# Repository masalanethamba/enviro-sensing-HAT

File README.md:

**GROUP 34**

**Description**

TheTemperature-Light sensor is a system that monitors and records
the temperature and light of a room or any place under consideration such that if the
temperature and the light are higher than required, the system displays it on the
computer. Similarly, if the temperature and the light are lower, the system displays it.
This System can also be connected to external Temperature/Light controllers.
Temperature/Light controller can be manual or automatic. The former requires full
human intervention to operate, while the latter requires little or not at all.
Furthermore, most temperature/light controller and related systems designed make
used of discrete components design such as timers, counters, decoder drivers and
thermistor temperature sensor and some use microcontrollers with external analogue
to digital converter (ADC) which is recommended for this system.
This system is powerful and very easy-to-program. It has 33-pins, and it has a
memory of 256-KB I2C of EEPROM data memory, self-programming.
Operating voltage range between 2V to 5V

**Getting Started with Temperature Sensor version5.1 and STM32CubeID**

**Introduction**
_________________________________________________________________________________

In this simple getting started how to document, we will be building a simple STM32CUBEID project (code) on a simple Temperature and Humidity Sensor uHAT. At its simplest/basic level the whole process of deploying  a code to the Temperature and Humidity Sensor PCB Version 5.1 consists of two “must do'' steps:

→ You would need to set your Temperature and Humidity Sensor with Group34OS, the  host OS which is responsible for  communication with the UCTCloud and also runs the core operations of the device

→  You need to also push your STM32CUBEID project image builder, which is responsible for pulling in all the important   
   dependencies and makes a container image for your fleet.
   
A completion of these steps implies that your Temperature and humidity Sensor Ver 5.1 will start to download the container image, begin your application, and start sending logs to your Group34 dashboard. This has got you at least a step towards success!

**What will you need?**
__________________________________________________________________________________
Hardware:

→ A Temperature and Humidity Sensor uHAT Ver5.1. You can also visit or GitHub repo and check out similar or related
                models.
                
→  18650-5V Li-ion battery for Power supply(optional) .

→ A simple micro USB mini cable for access to the CH340G transceiver and debugging

→ The micro USB can also be used for power supply.

→ Female connectors 

→ A syringe for water drops to acknowledge and appreciate the functionality of the sensors.

→ The STM32F051 UCT discovery board for the Cortex-M0 microcontroller interfacing.

→ A Group34 account/ link

→ Github account   

Software :
    →  STM32CUBEIDE
    
     →   Atollic and C are also alternatives but STM32CUBE IDE are strongly recommended

Setting up the Temperature and Humidity Sensor
 _________________________________________________________

Step1: Getting the overall view of the board

The overall view of the PCB is pretty much self explanatory, with the USB connector at the top and extended layer for the battery holder. On either side of the board there are 33x2 connectors, the first ones are female connectors  for mounting the uHAT on the UCT STM32F051 discovery board. The second are for debugging the board itself in a case of damaged pins. In Between the connectors there is a range of peripherals which include the two analog and digital sensors.

Overall View

Step2: Soldier and connect the female connectors on the board, These female connectors enable the PCB to be logged on the STM32f051 discovery board.
If soldered and connected correctly you have something like this: 

Step 3: Plugging the board to a power source.

This step is a 2 in 1 where we will be powering the PCB using the micro USB and deploying a code for the board to be able send information to the microcontroller.

Plugged board:

OPTIONAL:
The uHAT uses two sources of power, the USB and the Battery. You can also use the 5V Li-ion battery(18650)  but this step is optional because you would still need to connect the USB cable to send and receive information to the microcontroller. 

DEPLOYING THE CODE
________________________________________________________________________________________________________

This section covers the codes that are supposed to be written on the STM32CUBE IDE which sends this information (code) to the microcontroller, 

Step4 : Run the STM32CUBE IDE
Open and run the Stm32cube ide and copy and paste the following code on the references.
1.  

2.

3.

CONGRATULATIONS🥳, the Temperature and Humidity sensor is now fully functional, you can proceed to test the functionality of the board, we are looking forward to seeing you on version 6.

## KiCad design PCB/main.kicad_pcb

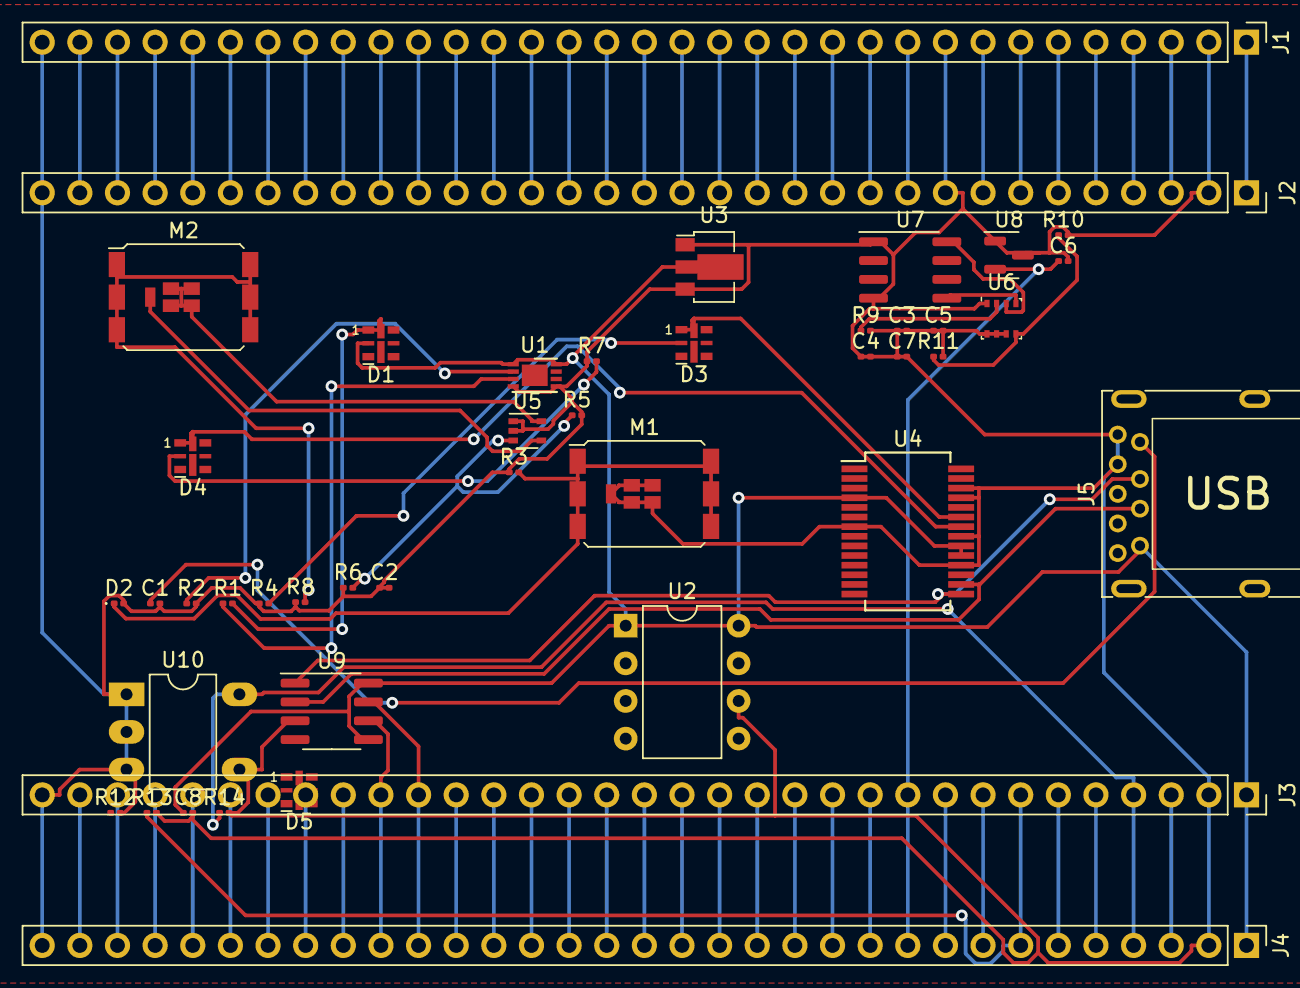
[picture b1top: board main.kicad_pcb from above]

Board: 2 copper layers, 44 parts (0 on the bottom side), 82 nets.

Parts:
C1, C8: 10nF; C_0201_0603Metric
C2: 10u; C_0201_0603Metric
C3, C4, C7: 10nf; C_0201_0603Metric
C5, C6: 0.1uF; C_0201_0603Metric
D1, D3, D4: LED_Small; LED-APA102-2020
D2: D_Zener; D_0201_0603Metric
D5: Blue; LED-APA102-2020
J1, J4: Conn_01x33_Female; PinHeader_1x33_P2.54mm_Vertical
J2, J3: Conn_01x33_Female; PinSocket_1x33_P2.54mm_Vertical
J5: USB_B_Micro; USB3_A_Molex_48393-001
M1, M2: MPMOS; DirectFET_L4
R1, R2, R3, R4, R6, R7, R8, R10, R11: 1K; R_0201_0603Metric
R5: 100; R_0201_0603Metric
R9: 4.7K; R_0201_0603Metric
R12: R; R_0201_0603Metric
R13, R14: 10K; R_0201_0603Metric
U1: MC34673; DFN-8-1EP_3x2mm_P0.5mm_EP1.75x1.45mm
U2: ADG417BN; DIP-8_W7.62mm
U3: HT75xx-1-SOT89; SOT-89-3
U4: FT232RL; SSOP-28_5.3x10.2mm_P0.65mm
U5: TLV172IDCK; SOT-353_SC-70-5
U6: BME280; Bosch_LGA-8_2.5x2.5mm_P0.65mm_ClockwisePinNumbering
U7: TSL2550D; SOIC-8_3.9x4.9mm_P1.27mm
U8: TC1047AxNB; SOT-23
U9: CH330N; SOIC-8_3.9x4.9mm_P1.27mm
U10: CAT24C256; DIP-5-6_W7.62mm_LongPads

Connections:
12C1_Clock: J3.4, J4.4, R14.1, U10.6 (SCL)
12C1_Data: J3.7, J4.7, R13.1
+3V0: J1.1, J2.1
+3V3: C1.2, C2.1, C2.2, C3.1, C3.2, C4.1, C4.2, C5.1, C5.2, C6.2, C7.1, C7.2, C8.2, D2.2 (A), J1.2, J1.9, J1.33, J2.2, J2.9, J2.33, J3.2, J3.33, J4.2, J4.33, J5.5 (GND), J5.6 (Shield), M1.2 (G), M1.3 (S), R2.2, R3.1, R4.1, R5.2, R6.1, R7.1, R8.1, R9.2, R10.2, R11.2, R12.2, R13.2, R14.2, U1.4 (~EN), U1.5 (GND), U2.6, U3.1 (GND), U3.3 (VOUT), U4.7 (GND), U4.18 (GND), U4.21 (GND), U4.25 (AGND), U4.26 (TEST), U5.1 (+), U5.2 (V-), U6.1 (GND), U6.6 (VDDIO), U6.7 (GND), U6.8 (VDD), U7.1 (VDD), U7.4 (GND), U8.1 (Vdd), U8.3 (GND), U9.3 (GND), U10.1 (A0), U10.2 (A1), U10.3 (A2), U10.4 (GND)
+5V: C8.1, D1.2 (A), D5.2 (A), J3.1, J4.1, J5.1 (VBUS), U1.1 (VIN), U1.8 (BAT), U2.1, U2.8, U3.2 (VIN), U4.4 (VCCIO), U4.19 (~RESET), U4.20 (VCC), U9.5 (VCC), U9.8 (V3)
/BOOT: J3.6, J4.6
/NRST: J1.10, J2.10
/PA0: J1.15, J2.15
/PA1: J1.16, J2.16
/PA2: J1.17, J2.17
/PA3: J1.18, J2.18
/PA4: J1.21, J2.21
/PA5: J1.22, J2.22
/PA6: J1.23, J2.23
/PA7: J1.24, J2.24
/PA8: J3.25, J4.25
/PA11: J3.22, J4.22
/PA12: J3.21, J4.21
/PA13: J3.20, J4.20
/PA14: J3.17, J4.17
/PA15: J3.16, J4.16
/PB0: J1.27, J2.27
/PB1: J1.28, J2.28
/PB2: J1.29, J2.29
/PB3: J3.11, J4.11
/PB5: J3.9, J4.9
/PB6: J3.8, J4.8
/PB9: J3.3, J4.3
/PB10: J1.30, J2.30
/PB11: J1.31, J2.31
/PB12: J1.32, J2.32
/PB13: J3.32, J4.32
/PB14: J3.31, J4.31
/PB15: J3.30, J4.30
/PC0: J1.11, J2.11
/PC1: J1.12, J2.12
/PC2: J1.13, J2.13
/PC3: J1.14, J2.14
/PC4: J1.25, J2.25
/PC5: J1.26, J2.26
/PC6: J3.29, J4.29
/PC7: J3.28, J4.28
/PC8: J3.27, J4.27
/PC9: J3.26, J4.26
/PC10: J3.15, J4.15
/PC11: J3.14, J4.14
/PC12: J3.13, J4.13
/PC13: J1.4, J2.4
/PC14: J1.5, J2.5
/PC15: J1.6, J2.6
/PD2: J3.12, J4.12
/PF0: J1.7, J2.7
/PF1: J1.8, J2.8
/PF4: J1.19, J2.19
/PF5: J1.20, J2.20
/PF6: J3.19, J4.19
/PF7: J3.18, J4.18
/VBAT: J1.3, J2.3
Anaolog_Out: C6.1, J3.10, J4.10, U8.2 (Vout)
I2C1_Data: U6.3 (SDI), U7.8 (DAT)
I2C2_Clock: U6.4 (SCK), U7.5 (CLK)
unnamed: C1.1, J5.4 (ID)
unnamed: D1.1 (K), R1.2
unnamed: D2.1 (K), M1.1 (D), R3.2
unnamed: D3.1 (K), U4.23 (CBUS0)
unnamed: D3.2 (A), R4.2
unnamed: D4.1 (K), U4.22 (CBUS1)
unnamed: D4.2 (A), R7.2
unnamed: D5.1 (K), R12.1
unnamed: M2.1 (D), R8.2
unnamed: M2.2 (G), U5.4
unnamed: M2.3 (S), U5.5 (V+)
unnamed: R1.1, U1.3 (~CHG)
unnamed: R2.1, U1.2 (~PPR)
unnamed: R5.1, R6.2, U5.3 (-)
unnamed: R9.1, U6.2 (CSB)
unnamed: R10.1, R11.1, U6.5 (SDO)
USART_RX: J3.23, J4.23, U9.7 (RXD)
USART_TX: J3.24, J4.24, U9.6 (TXD)
USB_D+: J5.3 (D+), U4.15 (USBD+), U9.1 (UD+)
USB_D-: J5.2 (D-), U4.16 (USBD-), U9.2 (UD-)
VDD: J3.5, J4.5

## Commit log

2022-02-26 Readme file updated
2022-03-20 Create CAD
2022-03-20 Create Docs
2022-03-20 Create Firmware
2022-03-20 Create PCB
2022-03-20 Create Production
2022-03-20 Create Simulation
2022-03-20 datasheets
2022-03-20 Create Docs,r
2022-03-20 The Datasheets of the IC used in the HAT design so far.
2022-03-20 Bills of Material for the modules individually and the combined main circuit
2022-04-08 Added the Library
2022-05-23 Update LICENSE
